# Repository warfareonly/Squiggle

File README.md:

This is a fork of ibnuda's Squiggle keyboard, with minor (aesthetic) changes
for myself!

# Squiggle Keyboard

It's a keyboard family which based on my circumstances, preferences, and
observed usages.

Requirements:

- 5 columns per hand.
  My right pinky is almost useless.
- At most 3 keys for each side's thumb row.
  My right thumb key is almost useless.
- No numrow.
  It's harder and more cumbersome to use than a numpad on a layer.
- Split.
  Typing on single flat keyboard hurts my arms in a lot of use cases.
- Symmetric.
  Personal preferences.

This family keyboard repo will not have any of the following features:

- OLED Screen: useless.
- LEDs: useless for me and hurt my eyes.
- Rotary Encoder: useless for me.
- Hotswap: I need a commitment.
- Case for `Low Profile`: defeating the whole purpose of ***LOW*** profile.

## Screenshot

### Standard

- MX and Alps style switches.
- 34 Keys.
- 4x2u thumb keys.
- 2 Promicros.
- TRRS/TRS cable.

### Low Profile

- Dongguan Kaihua Electronics Co., Ltd (originally named Longhua Electronics)'s
  Choc style switches.
- 34 Keys.
- 4x2u thumb keys.
- 2 Promicros.
- TRRS/TRS cable.

### 36 Keys

- MX and Alps style switches.
- 36 Keys.
- 4x2u+2x1.25u thumb keys.
- 2 Promicros.
- TRRS/TRS cable.

### Minimalist

- MX and Alps style switches.
- 34 Keys.
- 4x2u thumb keys.
- 1 Promicros.
- "Amphenol 10 wire" cable.

### Goldberg

(Because it's more complex than necessary. It's just a damn keyboard.)

- MX and Alps style switches.
- 34 - 38 Keys.
- 4x2u or 8x1u thumb keys. (or anything in between)
- 2 Promicros.
- TRRS/TRS cable.

## Disclaimer

I haven't printed some of it. But, theoretically, they should just work.
Oh, if things go wrong, I won't take any responisibilities.

## Additional Note

Any files with `mokou_*.kicad_mod` in `libs/footprints` are made by [Jokan Hiyou](https://twitter.com/jokanhiyou)
and belong to hers.
I just dither them and made them kicad footprints.

## License

GPLv3.

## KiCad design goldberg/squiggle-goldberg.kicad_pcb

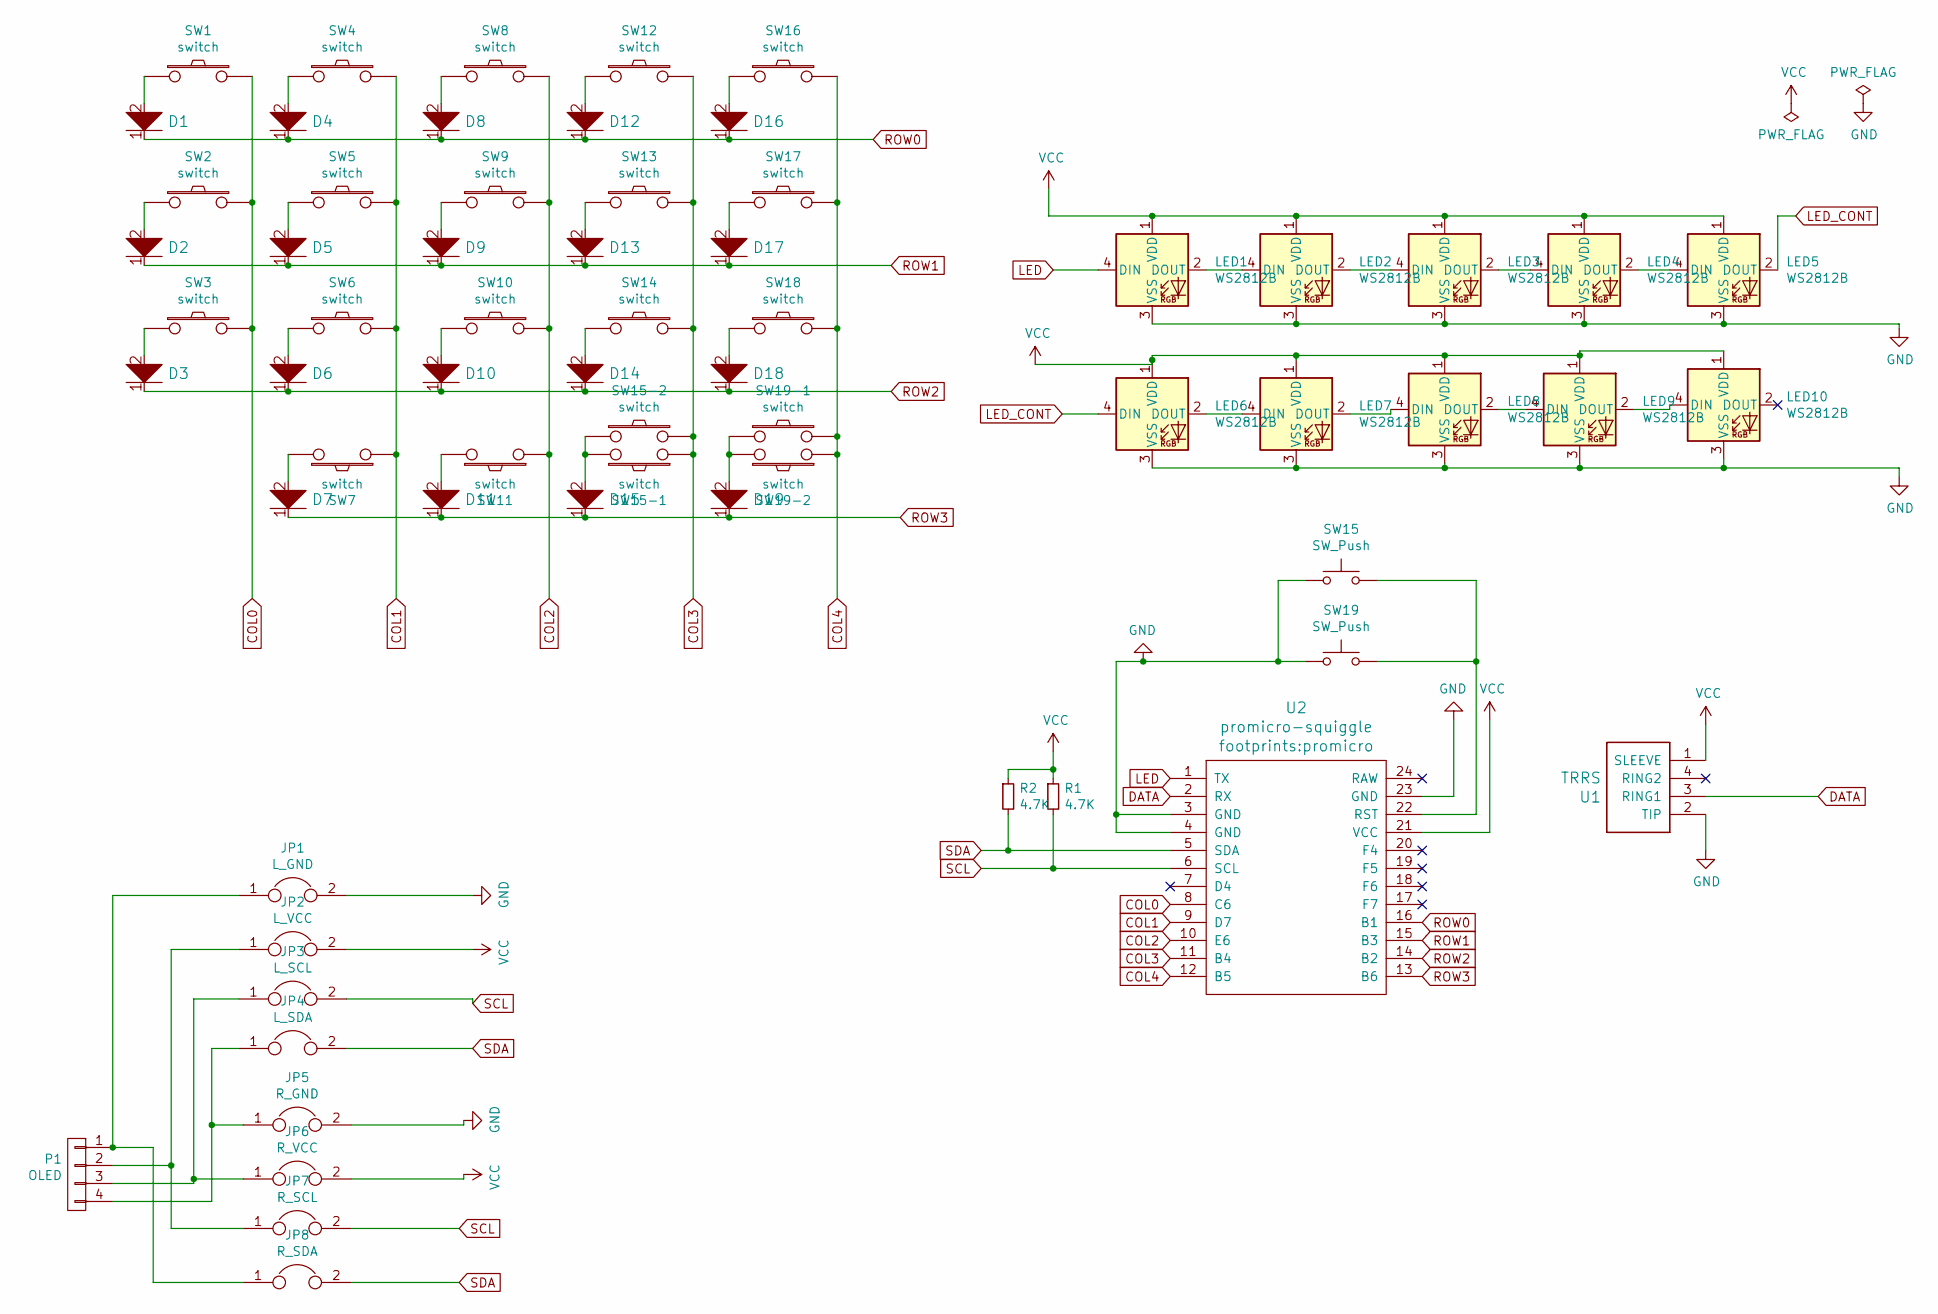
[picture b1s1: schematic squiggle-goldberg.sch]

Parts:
D1, D2, D3, D4, D5, D6, D7, D8, D9, D10, D11, D12, D13, D14, D15, D16, D17, D18, D19: D; diode
JP1: L_GND; Jumper
JP2: L_VCC; Jumper
JP3: L_SCL; Jumper
JP4: L_SDA; Jumper
JP5: R_GND; Jumper
JP6: R_VCC; Jumper
JP7: R_SCL; Jumper
JP8: R_SDA; Jumper
LED1, LED2, LED3, LED4, LED5, LED6, LED7, LED8, LED9, LED10: WS2812B; LED_WS2812B_4Pad
P1: OLED; SSD_1306_128x32
R1, R2: 4.7K; R_Axial_DIN0207_L6.3mm_D2.5mm_P10.16mm_Horizontal
SW1, SW2, SW3, SW4, SW5, SW6, SW7, SW8, SW9, SW10, SW11, SW12, SW13, SW14, SW15-2, SW16, SW17, SW18, SW19-2: switch; 1u-dual
SW15, SW19: SW_Push; SW_PUSH_6mm_H5mm
SW15-1, SW19-1: switch; 2u-dual
U1: TRRS; trrs
U2: promicro-squiggle; promicro

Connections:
COL0: SW1.2, SW2.2, SW3.2, U2.8 (C6)
COL1: SW4.2, SW5.2, SW6.2, SW7.1, U2.9 (D7)
COL2: SW8.2, SW9.2, SW10.2, SW11.1, U2.10 (E6)
COL3: SW12.2, SW13.2, SW14.2, SW15-1.1, SW15-2.2, U2.11 (B4)
COL4: SW16.2, SW17.2, SW18.2, SW19-1.2, SW19-2.1, U2.12 (B5)
DATA: U1.3 (RING1), U2.2 (RX)
GND: JP1.2, JP5.2, LED1.3 (VSS), LED2.3 (VSS), LED3.3 (VSS), LED4.3 (VSS), LED5.3 (VSS), LED6.3 (VSS), LED7.3 (VSS), LED8.3 (VSS), LED9.3 (VSS), LED10.3 (VSS), SW15.1, SW19.1, U1.2 (TIP), U2.3 (GND), U2.4 (GND), U2.23 (GND)
LED: LED1.4 (DIN), U2.1 (TX)
LED_CONT: LED5.2 (DOUT), LED6.4 (DIN)
unnamed: D1.2, SW1.1
unnamed: D2.2, SW2.1
unnamed: D3.2, SW3.1
unnamed: D4.2, SW4.1
unnamed: D5.2, SW5.1
unnamed: D6.2, SW6.1
unnamed: D7.2, SW7.2
unnamed: D8.2, SW8.1
unnamed: D9.2, SW9.1
unnamed: D10.2, SW10.1
unnamed: D11.2, SW11.2
unnamed: D12.2, SW12.1
unnamed: D13.2, SW13.1
unnamed: D14.2, SW14.1
unnamed: D15.2, SW15-1.2, SW15-2.1
unnamed: D16.2, SW16.1
unnamed: D17.2, SW17.1
unnamed: D18.2, SW18.1
unnamed: D19.2, SW19-1.1, SW19-2.2
unnamed: JP1.1, JP8.1, P1.1
unnamed: JP2.1, JP7.1, P1.2
unnamed: JP3.1, JP6.1, P1.3
unnamed: JP4.1, JP5.1, P1.4
unnamed: LED1.2 (DOUT), LED2.4 (DIN)
unnamed: LED2.2 (DOUT), LED3.4 (DIN)
unnamed: LED3.2 (DOUT), LED4.4 (DIN)
unnamed: LED4.2 (DOUT), LED5.4 (DIN)
unnamed: LED6.2 (DOUT), LED7.4 (DIN)
unnamed: LED7.2 (DOUT), LED8.4 (DIN)
unnamed: LED8.2 (DOUT), LED9.4 (DIN)
unnamed: LED9.2 (DOUT), LED10.4 (DIN)
unnamed: SW15.2, SW19.2, U2.22 (RST)
ROW0: D1.1, D4.1, D8.1, D12.1, D16.1, U2.16 (B1)
ROW1: D2.1, D5.1, D9.1, D13.1, D17.1, U2.15 (B3)
ROW2: D3.1, D6.1, D10.1, D14.1, D18.1, U2.14 (B2)
ROW3: D7.1, D11.1, D15.1, D19.1, U2.13 (B6)
SCL: JP3.2, JP7.2, R1.2, U2.6 (SCL)
SDA: JP4.2, JP8.2, R2.2, U2.5 (SDA)
VCC: JP2.2, JP6.2, LED1.1 (VDD), LED2.1 (VDD), LED3.1 (VDD), LED4.1 (VDD), LED5.1 (VDD), LED6.1 (VDD), LED7.1 (VDD), LED8.1 (VDD), LED9.1 (VDD), LED10.1 (VDD), R1.1, R2.1, U1.1 (SLEEVE), U2.21 (VCC)

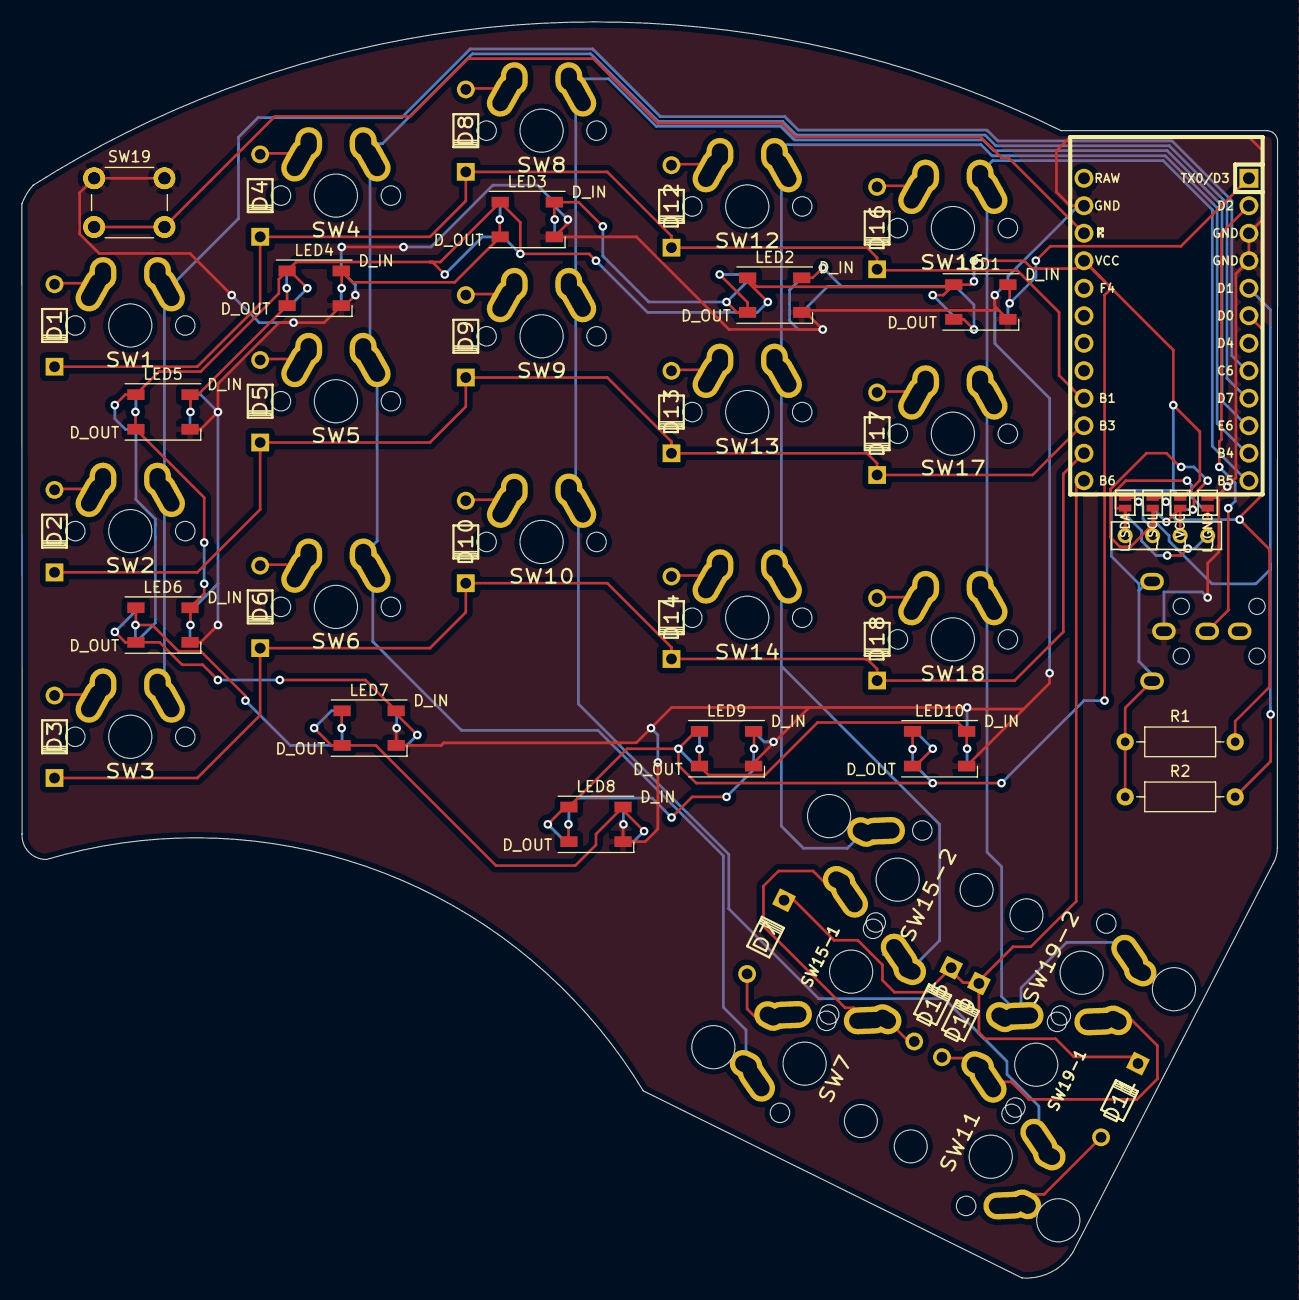
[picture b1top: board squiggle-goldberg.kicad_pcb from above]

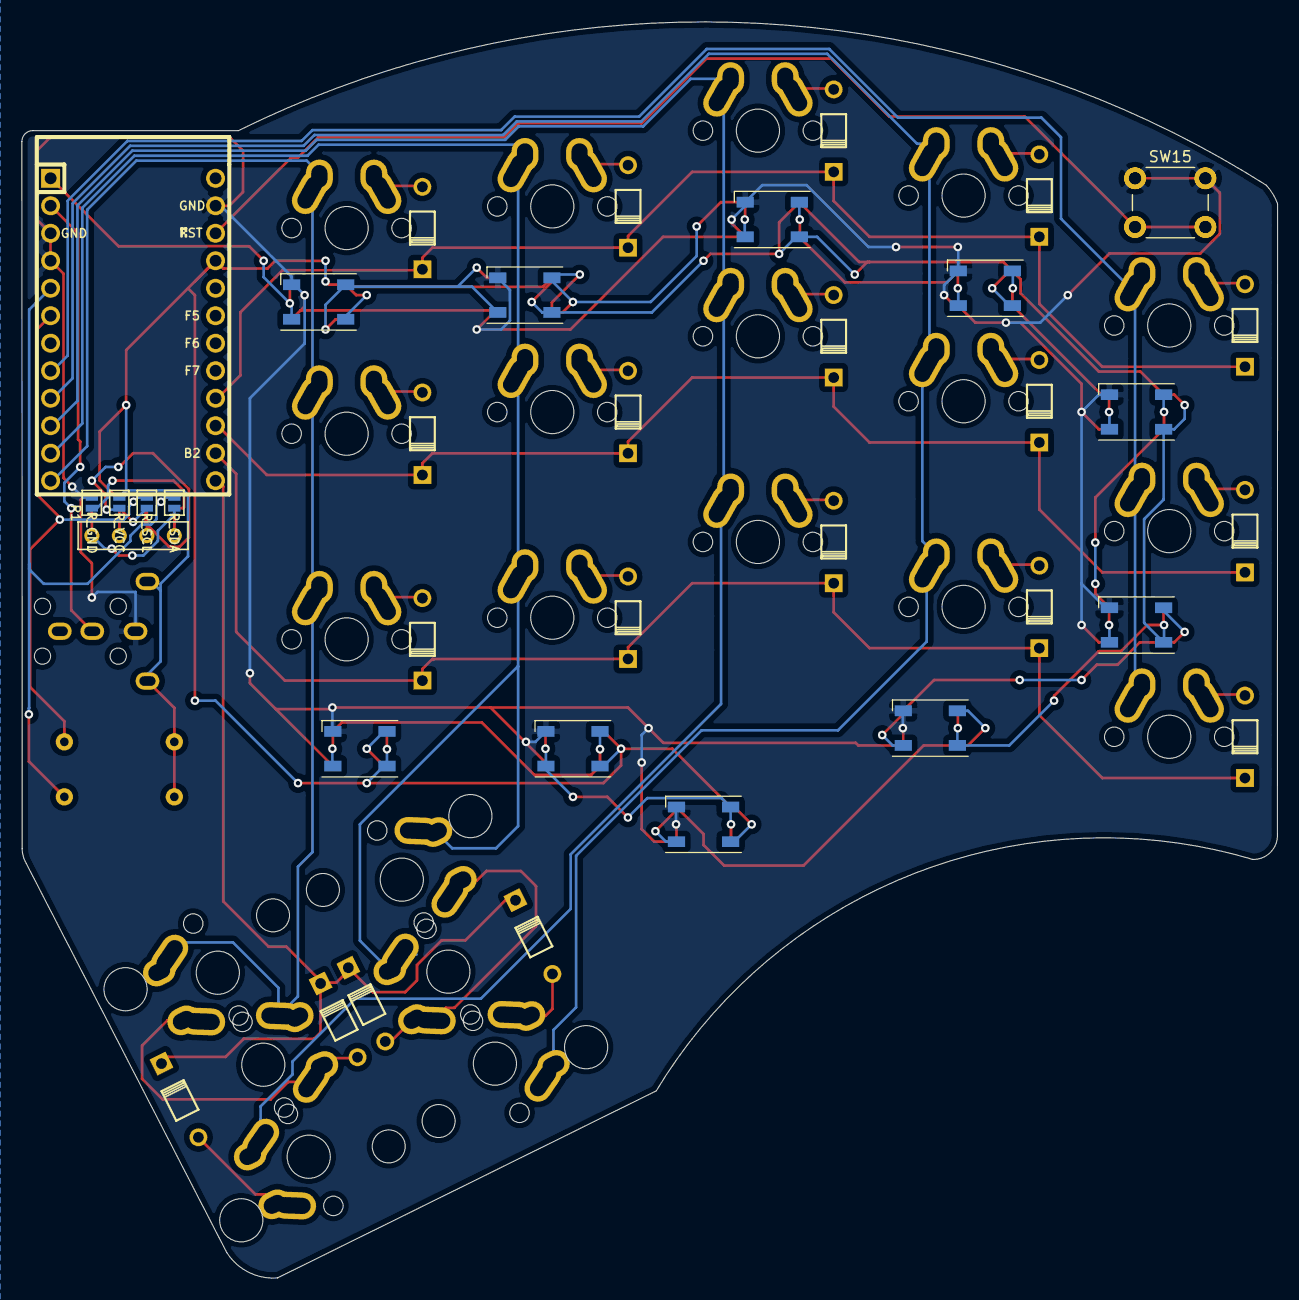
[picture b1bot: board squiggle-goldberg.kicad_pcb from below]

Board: 2 copper layers, 116.0 x 116.1 mm, 65 parts (8 on the bottom side), 48 nets.

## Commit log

2020-07-22 Modified the goldberg design files for myself
2020-07-22 Goldberg LP settings
2020-07-22 Updated the Goldberg PCB with correct memes
2020-07-22 Goldberg LP STLs
2020-07-24 Initial efforts towards adding I2C and LEDs
2020-07-27 Added footprints from ergoslab
2020-07-27 Added OLED
2020-07-27 Added 128x64 OLED footprint and LED footprint
2020-07-27 Updated PCB
2020-07-27 Libraries
2020-07-27 PC change
2020-07-27 Added LEDs and RESET button
2020-07-28 Added GND fill to both Cu layers
